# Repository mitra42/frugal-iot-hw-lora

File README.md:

# Frugal-IoT V0.3 LoRa

A simple, un-opinionated, multi-purpose sensor board, that can be wired to sensors using most common interfaces (I2C, ModBus, OneWire, Analog) with onboard charging and external antennas, plus a LoRa radio so boards can talk to each other where there is no WiFi.

This is the [Frugal-IoT V0.2 sensor board](https://github.com/mitra42/frugal-iot-hw-sensor) with an SX1262 LoRa radio added.

**Status:** laid out and routed, for review (31 Oct 2026): 84 × 37 mm, DRC clean, JLCPCB files ready but not ordered. About USD17.31 per board for 10 and USD11.58 for 100. See `DECISIONS.md` for requirements, decisions and the one open question (power budget with LoRa).

## Hardware Features

* ESP32-S3-WROOM-1U
* Ai-Thinker Ra-01SH LoRa radio (SX1262, 803–930 MHz), so one board covers AU915, AS923, IN865 and EU868 — the band is set in firmware.
* Two U.FL sockets for external antennas, one for WiFi (on the ESP32 module) and one for LoRa (on the radio module) — see [Antennas](#antennas).
* LoRa radio on its own always-on regulator, isolated from WiFi load and sleeping at under 1µA.
* USB-C for power and programming (e.g. using a $10 security camera solar panel)
* Protected charger circuitry for a single LiPo cell (~250mA), will work with really small cells (e.g. salvaged from vapes) or by adding a solder bridge can charge an 18650 cell at ~500mA
* Low-quiescent regulators (2µA each), so the board draws very little while asleep.
* Sensors controlled by a switched 3.3V sensor rail, allowing much lower power consumption in sleep.
* I2C support on J2
* Two sensor inputs on J2 (pins 6 & 9, GPIO4 & GPIO5) can be used for analog, OneWire etc, pads to add pull up resistor or smoothing capacitor if required.
* Two extra sensors on J3 (pins 6 & 9, GPIO1 & GPIO2)
* RS485(Modbus) on J3 pins 2 & 3, (can be omitted to save ~USD1.00, or the pins used as serial RX/TX instead).
* Six spare GPIOs on a 2 x 5 block of holes at the top edge, with GND and two switched 3.3V, for a header if ever needed.
* Test pads on every supply rail (VBUS, VBAT, VSYS, 3V3, 3V3_SW, 3V3_RF) and GND, labelled on the board.
* 37mm * 84mm board with connectors mostly at the ends, so that it can fit inside a 40mm pipe as an affordable enclosure.

## Antennas

Neither antenna is on the board or in `BOM.csv` (which is generated from the schematic) — buy them separately.

**Never transmit without the LoRa antenna connected**: the SX1262's output stage can be damaged driving an open socket.

The LoRa antenna plugs into the U.FL (IPEX MHF1) socket on the Ra-01SH. It must be a **50 Ω antenna for the
sub-GHz band** the board is configured for — 868 MHz (EU, Kenya, and 865–867 MHz India) or 915 MHz (Australia,
AS923 Indonesia). A 2.4 GHz WiFi antenna fits the same socket but works badly; the ESP32's own U.FL socket is
2.4 GHz, so label the two cables. Antennas marked "868/915" or "860–930 MHz" cover every region at some cost in
gain. When buying SMA parts, check SMA versus RP-SMA: they look alike and don't mate.

### Regular node

| Option | Parts | When |
|---|---|---|
| Whip through the end cap (recommended) | U.FL (MHF1) to SMA-female bulkhead pigtail, ~10–15 cm, 1.13 mm coax; 2–3 dBi SMA-male whip for the band | Nodes that relay for others or are far from their neighbours — range is the point of LoRa |
| Flexible PCB antenna inside the pipe | Adhesive FPC antenna with a U.FL lead | Short hops; no hole in the enclosure; cheapest. Expect less range: small FPC antennas are inefficient, so use the largest that fits |

Keep the antenna in a plastic (not metal) pipe, as far from the WiFi antenna, the cell and any wet soil as
the enclosure allows, and vertical if possible (nodes and gateway should share the same polarisation).

### Gateway node

The gateway is the same board (DECISIONS L11), but its antenna matters more because every node's traffic
passes through it.

* An outdoor omni antenna — fibreglass, 3–6 dBi, N-type, for the band (or 860–930 MHz), mast-mounted.
* Height beats gain: a few metres up, clear of roofs and trees, gains more than a higher-gain antenna low down.
* Keep the coax short. Thin cable loses several dB per metre at 900 MHz, so put the board (in its pipe) on the
  mast next to the antenna with a short pigtail, and run power or USB to it rather than RF. If a long RF run
  is unavoidable use low-loss coax (LMR-400 class).
* Seal the outdoor connectors (self-amalgamating tape) and earth the mast.
* Gain counts against the legal limit. With the SX1262 at its full +22 dBm, a 5.8 dBi antenna gives about
  28 dBm EIRP: inside Australia's 915–928 MHz limit (1 W EIRP) but far over Europe's 868 MHz limit
  (about 25 mW ERP in most sub-bands). Check the local rules (Kenya, India, Indonesia each set their own)
  and turn TX power down in firmware to match.

### Where to buy (low cost)

AliExpress listings, prices in USD as seen from Australia on 1 Nov 2026 without new-shopper deals; shipping
varies. Listings change and sellers' gain claims are optimistic, so check before ordering.

| For | Listing | Price | Per board |
|---|---|---|---|
| Node whip, 915 MHz | [NOWEPOCH, 3 dBi whip + U.FL-to-SMA bulkhead pigtail, pack of 4](https://www.aliexpress.com/item/1005008182646662.html) | 7.18 / 4 (6.35 at ≥10 packs) | 1.59–1.80 |
| Node whip, 868/915 MHz | [XYANT, 3 dBi whip + U.FL-to-SMA 15 cm pigtail, pack of 4](https://www.aliexpress.com/item/1005008633276903.html) | 7.79 / 4 (6.86 at ≥10 packs) | 1.72–1.95 |
| Node internal, 915 MHz | [CDEBYTE (Ebyte) TX915-FPC, 2.5 dBi, 10 per lot; sizes 3009, 4510, 7020, 8521 (length × width, mm)](https://www.aliexpress.com/item/1005010384153076.html) | 3.69–5.79 / 10 | 0.37–0.58 |
| Gateway antenna, 868 or 915 MHz | [GIZONT fibreglass omni, 35 cm, N-type, "5.8 dBi" (choose band variant)](https://www.aliexpress.com/item/1005012560449111.html) | 6.40–6.54 | — |
| Gateway pigtail | [U.FL (IPX1) to waterproof N-female bulkhead, RG178, 5 cm to 2 m](https://www.aliexpress.com/item/1005004546386028.html) | 3.60 (8 cm) | — |

Notes:
* For comparison, [Rokland's MHF1-to-SMA pigtails](https://store.rokland.com/products/2-pack-ufl-ipex4-mhf4-to-sma-female-pigtail-antenna-wifi-iot-dev-cable) alone are about USD 4 per board.
* The 868/915 whip is a compromise across both bands; the 915-only one should do a little better in AU/AS923.
* No 868 MHz version of the Ebyte FPC was found on AliExpress; for 868 regions use the whip, or find an 868 FPC.
  Choose the 8521 (85 × 21 mm) size if it fits — bigger is more efficient at sub-GHz.
* A real 5.8 dBi collinear at 868 MHz is usually much longer than 35 cm; treat the GIZONT as roughly 3 dBi.
  It is still a cheap, weatherproof outdoor antenna. Better-documented ones ([RAK](https://www.aliexpress.com/item/32852314761.html), [SparkFun](https://www.sparkfun.com/lora-fiberglass-antenna-type-n-5-8dbi-863-870mhz.html)) cost USD 40–120.
* RG178 loses roughly 1 dB per metre or more at 900 MHz: keep the gateway pigtail as short as the mounting allows.

## Software features

The board can be flashed with any software, but its designed to work well with [Frugal-IoT](https://github.com/mitra42/frugal-iot) which has the following features.

* Support for a very wide and expanding range of sensors
* Integrates with Frugal-IoT cloud, and UX on phone or laptop
* Plug and play MQTT interface, treats remote sensors and actuators the same as local ones
* LoRa mesh (using [LoRaMesher](https://github.com/LoRaMesher/LoRaMesher)), so sensors out of WiFi range report through other boards; any board can be the gateway to WiFi.
* Captive WiFi portal for local configuration
* Local controls for on-device automation configured through the UX.
* Multilingual support on both captive portal and UX
* Automatic Over-The-Air (OTA) updates for unattended devices (when on WiFi)
* Power management for really long life for sensors that report at long intervals.
* mDNS, for device to device signalling when the Internet is down
* NTP integration for accurate clock
* Fully Open-Source (i.e. not crippleware)

The radio is wired to the same ESP32-S3 pins as the Heltec WiFi LoRa 32 V3/V4, so firmware set up for those boards carries over.

## Files

| | |
|---|---|
| `SCHEMATIC.pdf` | schematic, one sheet |
| `BOM.csv` | bill of materials with LCSC (JLCPCB) part numbers; DNP = not fitted |
| `COST-ESTIMATE.txt` | JLCPCB cost for 10 and 100 boards, and the saving without Modbus |
| `PCB-LAYOUT.pdf` | 3D views and both copper layers |
| `fabrication/` | files to order from JLCPCB — see its README |
| `DECISIONS.md` | requirements, design decisions and why |
| `datasheets/` | Ai-Thinker Ra-01SH specification (Chinese; pinout, footprint and internal schematic) |
| `frugal_iot_v03/` | KiCad 10 project |
| `v0.2-baseline/` | the V0.2 board this started from: its README, decisions, schematic, layout, BOM, fabrication and firmware files |
| `claude-tools/` | scripts Claude uses to regenerate the design — reviewers can ignore |

The schematic is generated from `claude-tools/schematic/circuit.py`: changes made by Claude go there, not into
the .kicad_sch. Regenerate: `buildlib.py`, `run_draw_bg.sh` (log must end `VERIFY OK`), `run_kicad.sh`,
then `jlc_dump.sh` and `python3 cost_estimate.py > ../../COST-ESTIMATE.txt`.

If the fabrication and KiCad directories are not available wherever you find this, please let me know (mitra@mitra.biz) and I'll send you them.

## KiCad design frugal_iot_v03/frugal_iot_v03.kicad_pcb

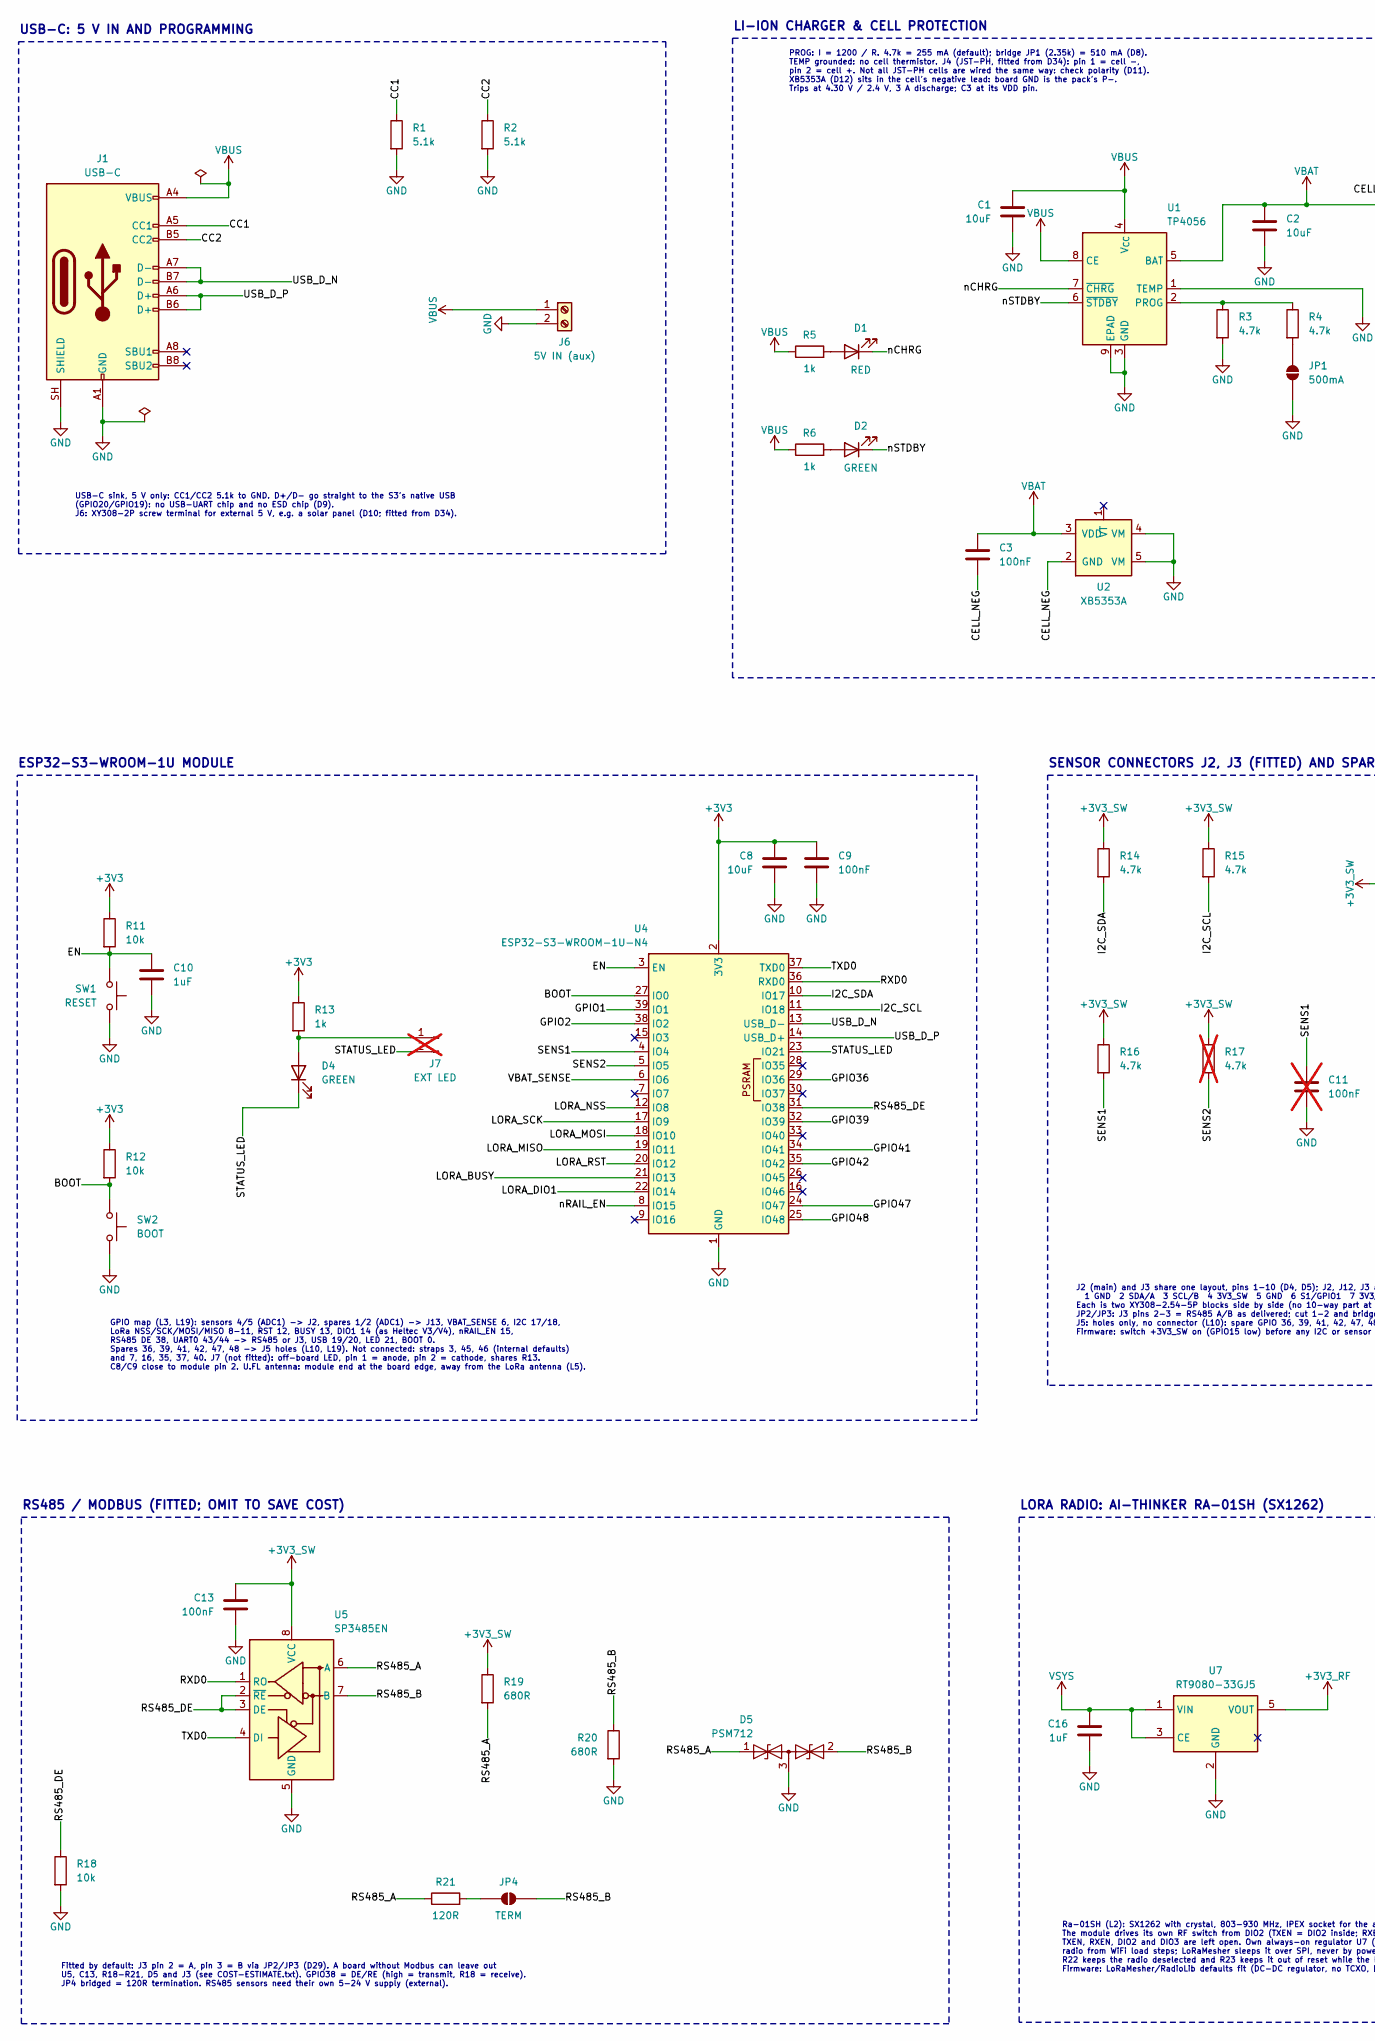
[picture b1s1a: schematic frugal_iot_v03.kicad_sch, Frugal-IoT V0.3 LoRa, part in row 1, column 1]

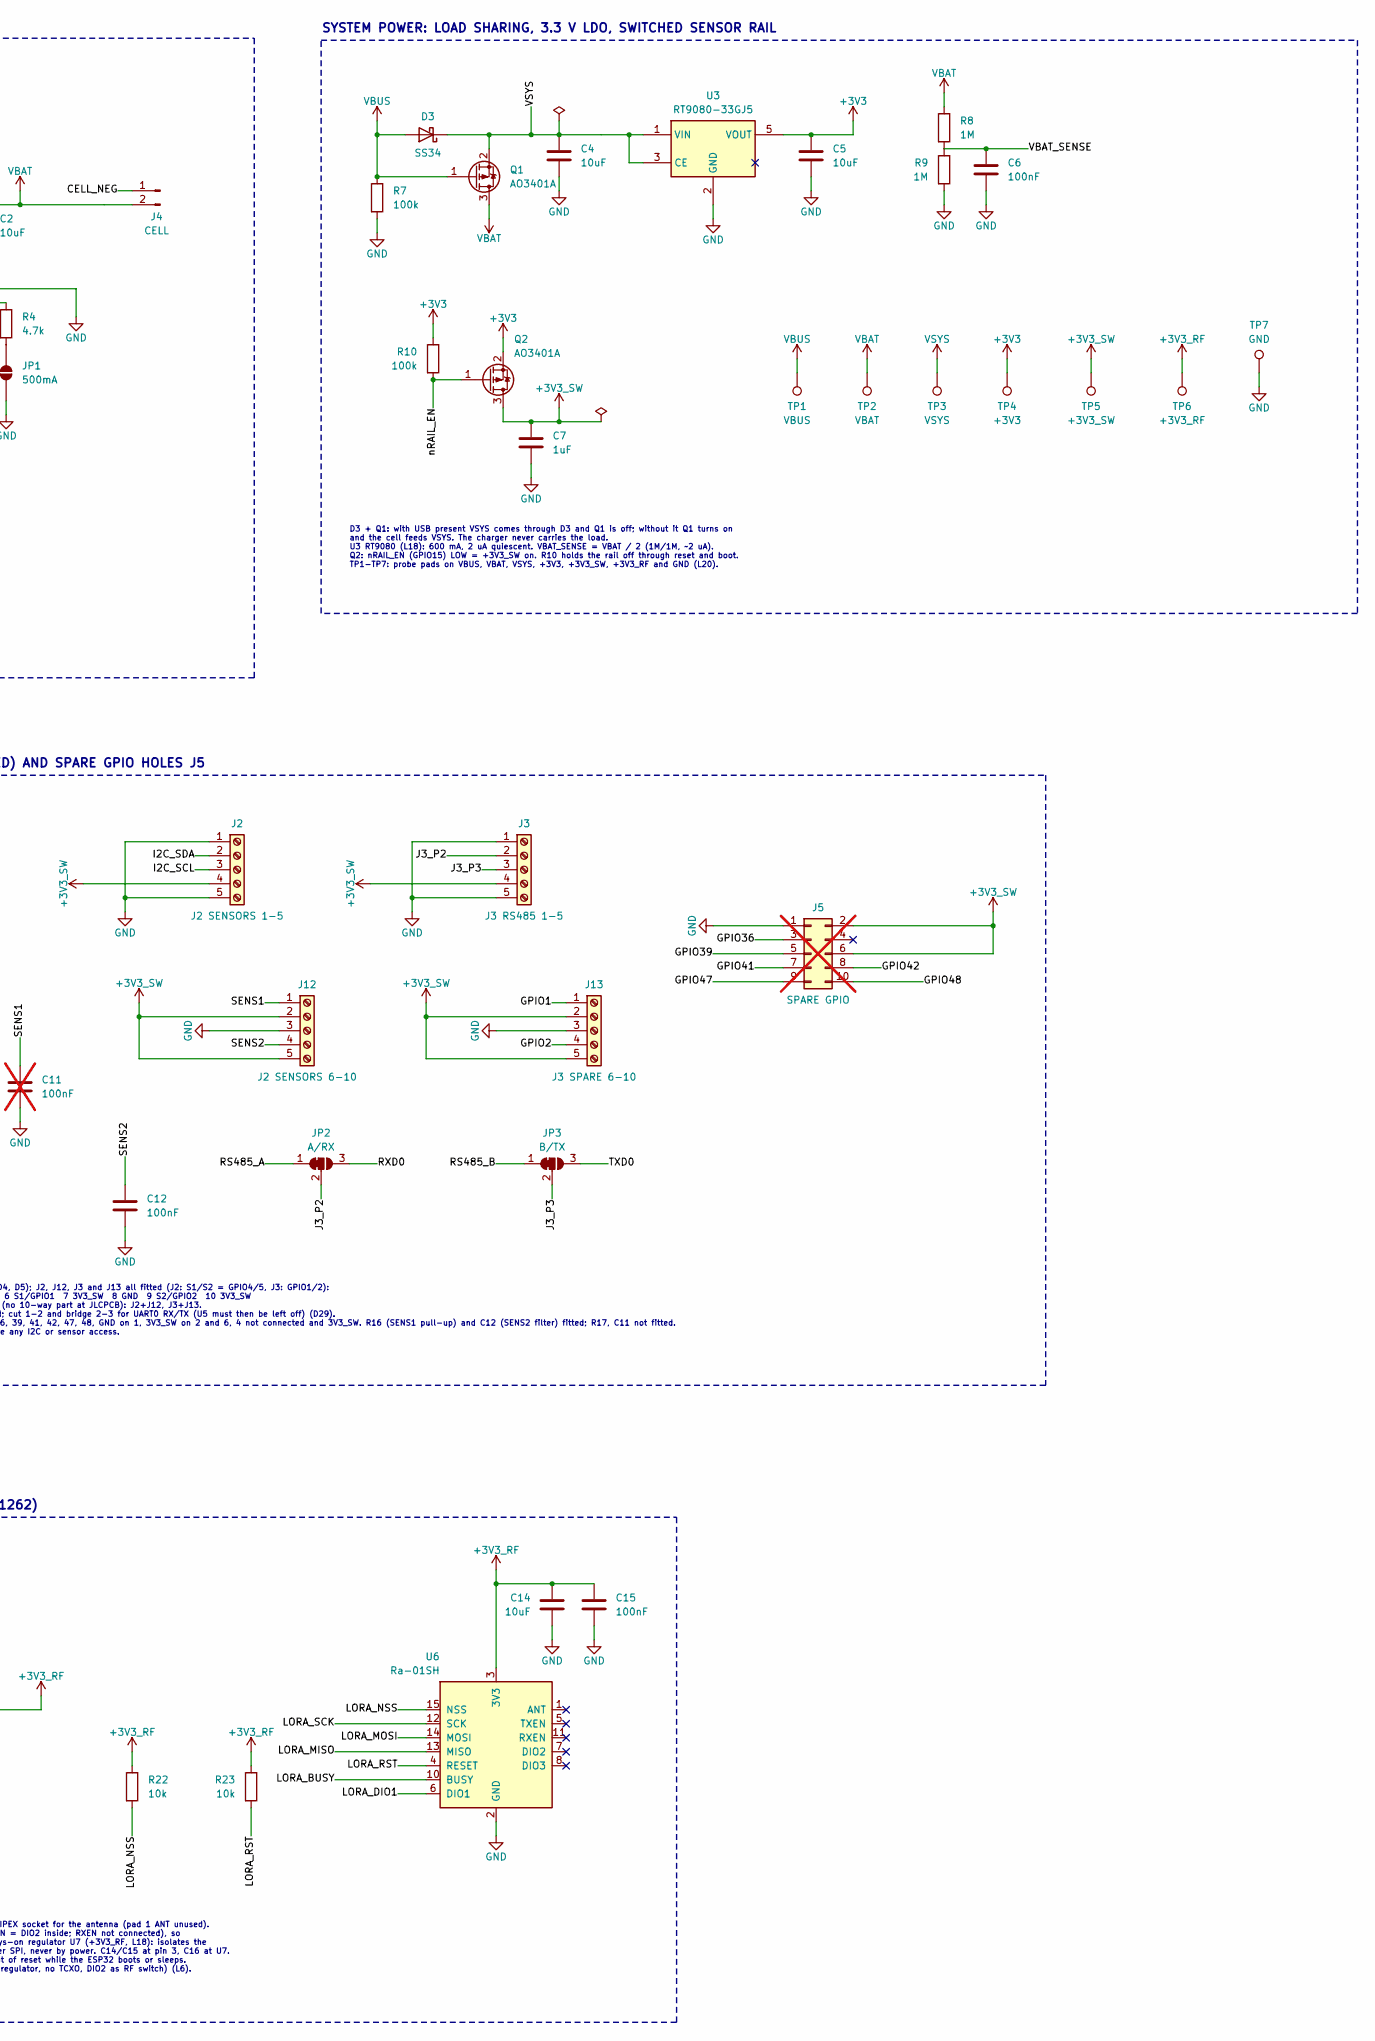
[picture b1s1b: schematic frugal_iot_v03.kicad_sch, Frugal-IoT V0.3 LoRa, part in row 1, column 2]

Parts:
C1, C2, C4, C5, C8, C14: 10uF; C_0603_1608Metric; MPN 10uF; LCSC C19702
C3, C6, C9, C12, C13, C15: 100nF; C_0603_1608Metric; MPN 100nF; LCSC C14663
C7, C10, C16: 1uF; C_0603_1608Metric; MPN 1uF; LCSC C15849
C11: 100nF; C_0603_1608Metric; MPN 100nF; LCSC C14663; not fitted
D1: RED; LED_0603_1608Metric; MPN KT-0603R; LCSC C2286
D2, D4: GREEN; LED_0805_2012Metric; MPN KT-0805G; LCSC C2297
D3: SS34; D_SMA; MPN SS34; LCSC C8678
D5: PSM712; SOT-23; MPN PSM712-LF-T7; LCSC C32677
J1: USB-C; USB_C_Receptacle_HRO_TYPE-C-31-M-12; MPN TYPE-C-31-M-12; LCSC C165948
J2: J2 SENSORS 1-5; TerminalBlock_Xinya_XY308-2.54-5P_1x05_P2.54mm_Horizontal; MPN XY308-2.54-5P; LCSC C915914
J3: J3 RS485 1-5; TerminalBlock_Xinya_XY308-2.54-5P_1x05_P2.54mm_Horizontal; MPN XY308-2.54-5P; LCSC C915914
J4: CELL; JST_PH_S2B-PH-K_1x02_P2.00mm_Horizontal; MPN S2B-PH-K-S; LCSC C173752
J5: SPARE GPIO; PinHeader_2x05_P2.54mm_Vertical; MPN SPARE GPIO; not fitted
J6: 5V IN (aux); TerminalBlock_Xinya_XY308-2.54-2P_1x02_P2.54mm_Horizontal; MPN XY308-2.54-2P; LCSC C557685
J7: EXT LED; PinHeader_1x02_P2.54mm_Vertical; MPN EXT LED; not fitted
J12: J2 SENSORS 6-10; TerminalBlock_Xinya_XY308-2.54-5P_1x05_P2.54mm_Horizontal; MPN XY308-2.54-5P; LCSC C915914
J13: J3 SPARE 6-10; TerminalBlock_Xinya_XY308-2.54-5P_1x05_P2.54mm_Horizontal; MPN XY308-2.54-5P; LCSC C915914
JP1: 500mA; SolderJumper-2_P1.3mm_Open_RoundedPad1.0x1.5mm; MPN 500mA
JP2: A/RX; SolderJumper-3_P1.3mm_Bridged12_RoundedPad1.0x1.5mm; MPN A/RX
JP3: B/TX; SolderJumper-3_P1.3mm_Bridged12_RoundedPad1.0x1.5mm; MPN B/TX
JP4: TERM; SolderJumper-2_P1.3mm_Open_RoundedPad1.0x1.5mm; MPN TERM
Q1, Q2: AO3401A; SOT-23; MPN AO3401A; LCSC C15127
R1, R2: 5.1k; R_0603_1608Metric; MPN 5.1k; LCSC C23186
R3, R4, R14, R15, R16: 4.7k; R_0603_1608Metric; MPN 4.7k; LCSC C23162
R5, R6, R13: 1k; R_0603_1608Metric; MPN 1k; LCSC C21190
R7, R10: 100k; R_0603_1608Metric; MPN 100k; LCSC C25803
R8, R9: 1M; R_0603_1608Metric; MPN 1M; LCSC C22935
R11, R12, R18, R22, R23: 10k; R_0603_1608Metric; MPN 10k; LCSC C25804
R17: 4.7k; R_0603_1608Metric; MPN 4.7k; LCSC C23162; not fitted
R19, R20: 680R; R_0603_1608Metric; MPN 680R; LCSC C23228
R21: 120R; R_0603_1608Metric; MPN 120R; LCSC C22787
SW1: RESET; SW_Push_1P1T_XKB_TS-1187A; MPN TS-1187A-B-A-B; LCSC C318884
SW2: BOOT; SW_Push_1P1T_XKB_TS-1187A; MPN TS-1187A-B-A-B; LCSC C318884
TP1: VBUS; TestPoint_Pad_D1.5mm; MPN VBUS
TP2: VBAT; TestPoint_Pad_D1.5mm; MPN VBAT
TP3: VSYS; TestPoint_Pad_D1.5mm; MPN VSYS
TP4: +3V3; TestPoint_Pad_D1.5mm; MPN +3V3
TP5: +3V3_SW; TestPoint_Pad_D1.5mm; MPN +3V3_SW
TP6: +3V3_RF; TestPoint_Pad_D1.5mm; MPN +3V3_RF
TP7: GND; TestPoint_Pad_D1.5mm; MPN GND
U1: TP4056; SOIC-8-1EP_3.9x4.9mm_P1.27mm_EP2.41x3.3mm; MPN TP4056; LCSC C16581
U2: XB5353A; SOT-23-5; MPN XB5353A; LCSC C80628
U3, U7: RT9080-33GJ5; TSOT-23-5; MPN RT9080-33GJ5; LCSC C841192
U4: ESP32-S3-WROOM-1U-N4; ESP32-S3-WROOM-1U; MPN ESP32-S3-WROOM-1U-N4; LCSC C2980296
U5: SP3485EN; SOIC-8_3.9x4.9mm_P1.27mm; MPN SP3485EN-L/TR; LCSC C8963
U6: Ra-01SH; Ai-Thinker-Ra-01SH; MPN Ra-01SH; LCSC C2764087

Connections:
+3V3: C5.1, C8.1, C9.1, Q2.2 (S), R10.1, R11.1, R12.1, R13.1, TP4.1, U3.5 (VOUT), U4.2 (3V3)
+3V3_RF: C14.1, C15.1, R22.1, R23.1, TP6.1, U6.3 (3V3), U7.5 (VOUT)
/BOOT: R12.2, SW2.1, U4.27 (IO0)
/CC1: J1.A5 (CC1), R1.1
/CC2: J1.B5 (CC2), R2.1
/CELL_NEG: C3.2, J4.1, U2.2 (GND)
/EN: C10.1, R11.2, SW1.1, U4.3 (EN)
/GPIO1: J13.1, U4.39 (IO1)
/GPIO2: J13.4, U4.38 (IO2)
/GPIO36: J5.3, U4.29 (IO36)
/GPIO39: J5.5, U4.32 (IO39)
/GPIO41: J5.7, U4.34 (IO41)
/GPIO42: J5.8, U4.35 (IO42)
/GPIO47: J5.9, U4.24 (IO47)
/GPIO48: J5.10, U4.25 (IO48)
/I2C_SCL: J2.3, R15.2, U4.11 (IO18)
/I2C_SDA: J2.2, R14.2, U4.10 (IO17)
/J3_P2: J3.2, JP2.2 (C)
/J3_P3: J3.3, JP3.2 (C)
/LORA_BUSY: U4.21 (IO13), U6.10 (BUSY)
/LORA_DIO1: U4.22 (IO14), U6.6 (DIO1)
/LORA_MISO: U4.19 (IO11), U6.13 (MISO)
/LORA_MOSI: U4.18 (IO10), U6.14 (MOSI)
/LORA_NSS: R22.2, U4.12 (IO8), U6.15 (NSS)
/LORA_RST: R23.2, U4.20 (IO12), U6.4 (RESET)
/LORA_SCK: U4.17 (IO9), U6.12 (SCK)
/RS485_A: D5.1 (A1), JP2.1 (A), R19.2, R21.1, U5.6 (A)
/RS485_B: D5.2 (A2), JP3.1 (A), JP4.2 (B), R20.1, U5.7 (B)
/RS485_DE: R18.1, U4.31 (IO38), U5.2 (~RE), U5.3 (DE)
/RXD0: JP2.3 (B), U4.36 (RXD0), U5.1 (RO)
/SENS1: C11.1, J12.1, R16.2, U4.4 (IO4)
/SENS2: C12.1, J12.4, R17.2, U4.5 (IO5)
/STATUS_LED: D4.1 (K), J7.2, U4.23 (IO21)
/TXD0: JP3.3 (B), U4.37 (TXD0), U5.4 (DI)
/USB_D_N: J1.A7 (D-), J1.B7 (D-), U4.13 (USB_D-)
/USB_D_P: J1.A6 (D+), J1.B6 (D+), U4.14 (USB_D+)
/VBAT_SENSE: C6.1, R8.2, R9.1, U4.6 (IO6)
/nCHRG: D1.1 (K), U1.7 (~CHRG)
/nRAIL_EN: Q2.1 (G), R10.2, U4.8 (IO15)
/nSTDBY: D2.1 (K), U1.6 (~STDBY)
unnamed: D1.2 (A), R5.2
unnamed: D2.2 (A), R6.2
unnamed: D4.2 (A), J7.1, R13.2
unnamed: JP1.1 (A), R4.2
unnamed: JP4.1 (A), R21.2
unnamed: R3.1, R4.1, U1.2 (PROG)
VBAT: C2.1, C3.1, J4.2, Q1.3 (D), R8.1, TP2.1, U1.5 (BAT), U2.3 (VDD)

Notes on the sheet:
J2 (main) and J3 share one layout, pins 1-10 (D4, D5); J2, J12, J3 and J13 all fitted (J2: S1/S2 = GPIO4/5, J3: GPIO1/2): 1 GND 2 SDA/A 3 SCL/B 4 3V3_SW 5 GND 6 S1/GPIO1 7 3V3_SW 8 GND 9 S2/GPIO2 10 3V3_SW Each is two XY308-2.54-5P blocks side by side (no 10-way part at JLCPCB): J2+J12, J3+J13. JP2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
USB-C sink, 5 V only: CC1/CC2 5.1k to GND. D+/D- go straight to the S3's native USB (GPIO20/GPIO19): no USB-UART chip and no ESD chip (D9). J6: XY308-2P screw terminal for external 5 V, e.g. a solar panel (D10; fitted from D34).
PROG: I = 1200 / R. 4.7k = 255 mA (default); bridge JP1 (2.35k) = 510 mA (D8). TEMP grounded: no cell thermistor. J4 (JST-PH, fitted from D34): pin 1 = cell -, pin 2 = cell +. Not all JST-PH cells are wired the same way: check polarity (D11). XB5353A (D12) sits in the cell's negative lead: board GN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
ESP32-S3-WROOM-1U MODULE
Ra-01SH (L2): SX1262 with crystal, 803-930 MHz, IPEX socket for the antenna (pad 1 ANT unused). The module drives its own RF switch from DIO2 (TXEN = DIO2 inside; RXEN not connected), so TXEN, RXEN, DIO2 and DIO3 are left open. Own always-on regulator U7 (+3V3_RF, L18): isolates the radio from WiFi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
Fitted by default: J3 pin 2 = A, pin 3 = B via JP2/JP3 (D29). A board without Modbus can leave out U5, C13, R18-R21, D5 and J3 (see COST-ESTIMATE.txt). GPIO38 = DE/RE (high = transmit, R18 = receive). JP4 bridged = 120R termination. RS485 sensors need their own 5-24 V supply (external).
USB-C: 5 V IN AND PROGRAMMING
SYSTEM POWER: LOAD SHARING, 3.3 V LDO, SWITCHED SENSOR RAIL
LORA RADIO: AI-THINKER RA-01SH (SX1262)
GPIO map (L3, L19): sensors 4/5 (ADC1) -> J2, spares 1/2 (ADC1) -> J13, VBAT_SENSE 6, I2C 17/18, LoRa NSS/SCK/MOSI/MISO 8-11, RST 12, BUSY 13, DIO1 14 (as Heltec V3/V4), nRAIL_EN 15, RS485 DE 38, UART0 43/44 -> RS485 or J3, USB 19/20, LED 21, BOOT 0. Spares 36, 39, 41, 42, 47, 48 -> J5 holes (L10, 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
RS485 / MODBUS (FITTED; OMIT TO SAVE COST)
SENSOR CONNECTORS J2, J3 (FITTED) AND SPARE GPIO HOLES J5
D3 + Q1: with USB present VSYS comes through D3 and Q1 is off; without it Q1 turns on and the cell feeds VSYS. The charger never carries the load. U3 RT9080 (L18): 600 mA, 2 uA quiescent. VBAT_SENSE = VBAT / 2 (1M/1M, ~2 uA). Q2: nRAIL_EN (GPIO15) LOW = +3V3_SW on. R10 holds the rail off through re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
LI-ION CHARGER & CELL PROTECTION

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
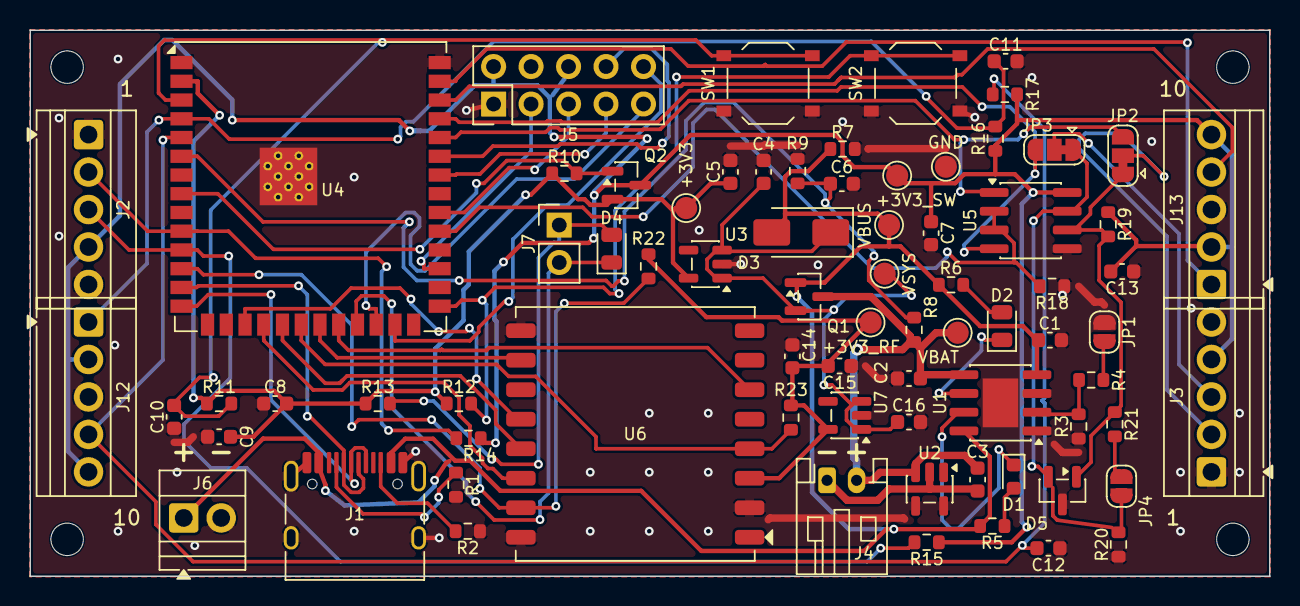
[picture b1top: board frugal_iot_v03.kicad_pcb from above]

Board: 2 copper layers, 84.0 x 37.0 mm, 79 parts (0 on the bottom side), 51 nets.

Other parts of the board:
H1, H2, H3, H4: M2; MountingHole_2.2mm_M2

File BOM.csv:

"Refs","Value","MPN","LCSC","Footprint","Qty","DNP","Note"
"C1,C2,C4,C5,C8,C14","10uF","10uF","C19702","Capacitor_SMD:C_0603_1608Metric","6","",""
"C3,C6,C9,C12,C13,C15","100nF","100nF","C14663","Capacitor_SMD:C_0603_1608Metric","6","","filter (analog)"
"C7,C10,C16","1uF","1uF","C15849","Capacitor_SMD:C_0603_1608Metric","3","","U7 input, close to its VIN"
"C11","100nF","100nF","C14663","Capacitor_SMD:C_0603_1608Metric","1","DNP","filter option (analog)"
"D1","RED","KT-0603R","C2286","LED_SMD:LED_0603_1608Metric","1","",""
"D2,D4","GREEN","KT-0805G","C2297","LED_SMD:LED_0805_2012Metric","2","",""
"D3","SS34","SS34","C8678","Diode_SMD:D_SMA","1","",""
"D5","PSM712","PSM712-LF-T7","C32677","Package_TO_SOT_SMD:SOT-23","1","",""
"J1","USB-C","TYPE-C-31-M-12","C165948","Connector_USB:USB_C_Receptacle_HRO_TYPE-C-31-M-12","1","",""
"J2","J2 SENSORS 1-5","XY308-2.54-5P","C915914","TerminalBlock:TerminalBlock_Xinya_XY308-2.54-5P_1x05_P2.54mm_Horizontal","1","",""
"J3","J3 RS485 1-5","XY308-2.54-5P","C915914","TerminalBlock:TerminalBlock_Xinya_XY308-2.54-5P_1x05_P2.54mm_Horizontal","1","",""
"J4","CELL","S2B-PH-K-S","C173752","Connector_JST:JST_PH_S2B-PH-K_1x02_P2.00mm_Horizontal","1","",""
"J5","SPARE GPIO","SPARE GPIO","","Connector_PinHeader_2.54mm:PinHeader_2x05_P2.54mm_Vertical","1","DNP","holes only (L10)"
"J6","5V IN (aux)","XY308-2.54-2P","C557685","TerminalBlock:TerminalBlock_Xinya_XY308-2.54-2P_1x02_P2.54mm_Horizontal","1","",""
"J7","EXT LED","EXT LED","","Connector_PinHeader_2.54mm:PinHeader_1x02_P2.54mm_Vertical","1","DNP","off-board LED: 1 = anode, 2 = cathode"
"J12","J2 SENSORS 6-10","XY308-2.54-5P","C915914","TerminalBlock:TerminalBlock_Xinya_XY308-2.54-5P_1x05_P2.54mm_Horizontal","1","",""
"J13","J3 SPARE 6-10","XY308-2.54-5P","C915914","TerminalBlock:TerminalBlock_Xinya_XY308-2.54-5P_1x05_P2.54mm_Horizontal","1","",""
"JP1","500mA","500mA","","Jumper:SolderJumper-2_P1.3mm_Open_RoundedPad1.0x1.5mm","1","",""
"JP2","A/RX","A/RX","","Jumper:SolderJumper-3_P1.3mm_Bridged12_RoundedPad1.0x1.5mm","1","",""
"JP3","B/TX","B/TX","","Jumper:SolderJumper-3_P1.3mm_Bridged12_RoundedPad1.0x1.5mm","1","",""
"JP4","TERM","TERM","","Jumper:SolderJumper-2_P1.3mm_Open_RoundedPad1.0x1.5mm","1","",""
"Q1,Q2","AO3401A","AO3401A","C15127","Package_TO_SOT_SMD:SOT-23","2","",""
"R1,R2","5.1k","5.1k","C23186","Resistor_SMD:R_0603_1608Metric","2","",""
"R3,R4,R14-R16","4.7k","4.7k","C23162","Resistor_SMD:R_0603_1608Metric","5","","pull-up (e.g. DS18B20),with JP1: ~500 mA,~250 mA"
"R5,R6,R13","1k","1k","C21190","Resistor_SMD:R_0603_1608Metric","3","",""
"R7,R10","100k","100k","C25803","Resistor_SMD:R_0603_1608Metric","2","","rail off at reset"
"R8,R9","1M","1M","C22935","Resistor_SMD:R_0603_1608Metric","2","",""
"R11,R12,R18,R22,R23","10k","10k","C25804","Resistor_SMD:R_0603_1608Metric","5","","radio deselected while the ESP32 boots or sleeps,radio out of reset while the ESP32 sleeps,receive by default"
"R17","4.7k","4.7k","C23162","Resistor_SMD:R_0603_1608Metric","1","DNP","pull-up option (e.g. DS18B20)"
"R19,R20","680R","680R","C23228","Resistor_SMD:R_0603_1608Metric","2","","bias"
"R21","120R","120R","C22787","Resistor_SMD:R_0603_1608Metric","1","",""
"SW1","RESET","TS-1187A-B-A-B","C318884","Button_Switch_SMD:SW_Push_1P1T_XKB_TS-1187A","1","",""
"SW2","BOOT","TS-1187A-B-A-B","C318884","Button_Switch_SMD:SW_Push_1P1T_XKB_TS-1187A","1","",""
"TP1","VBUS","VBUS","","TestPoint:TestPoint_Pad_D1.5mm","1","",""
"TP2","VBAT","VBAT","","TestPoint:TestPoint_Pad_D1.5mm","1","",""
"TP3","VSYS","VSYS","","TestPoint:TestPoint_Pad_D1.5mm","1","",""
"TP4","+3V3","+3V3","","TestPoint:TestPoint_Pad_D1.5mm","1","",""
"TP5","+3V3_SW","+3V3_SW","","TestPoint:TestPoint_Pad_D1.5mm","1","",""
"TP6","+3V3_RF","+3V3_RF","","TestPoint:TestPoint_Pad_D1.5mm","1","",""
"TP7","GND","GND","","TestPoint:TestPoint_Pad_D1.5mm","1","",""
"U1","TP4056","TP4056","C16581","Package_SO:SOIC-8-1EP_3.9x4.9mm_P1.27mm_EP2.41x3.3mm","1","","TEMP grounded: no cell NTC"
"U2","XB5353A","XB5353A","C80628","Package_TO_SOT_SMD:SOT-23-5","1","",""
"U3,U7","RT9080-33GJ5","RT9080-33GJ5","C841192","Package_TO_SOT_SMD:TSOT-23-5","2","",""
"U4","ESP32-S3-WROOM-1U-N4","ESP32-S3-WROOM-1U-N4","C2980296","RF_Module:ESP32-S3-WROOM-1U","1","",""
"U5","SP3485EN","SP3485EN-L/TR","C8963","Package_SO:SOIC-8_3.9x4.9mm_P1.27mm","1","",""
"U6","Ra-01SH","Ra-01SH","C2764087","frugal:Ai-Thinker-Ra-01SH","1","",""

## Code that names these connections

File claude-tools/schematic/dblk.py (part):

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        S.wire(pa, (xj, pa[1])); S.wire(pb, (xj, pb[1])); S.wire((xj, pa[1]), (xj, pb[1]))
        qa, qb = pin('J1', 'A6'), pin('J1', 'B6')
        S.wire(qa, (xj, qa[1])); S.wire(qb, (xj, qb[1])); S.wire((xj, qa[1]), (xj, qb[1]))
        S.wire((xj, pb[1]), (xj + 7.62, pb[1])); S.label('USB_D_N', xj + 7.62, pb[1])
        S.wire((xj, qa[1]), (xj + 7.62, qa[1])); S.label('USB_D_P', xj + 7.62, qa[1])
        # CC pull-downs
        cx = n1[0] + 30.48
        for ref, net in (('R1', 'CC1'), ('R2', 'CC2')):
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        c = at(n, -10.16)
        S.wire(n, c)
        cb = hang('C3', c)
        S.wire(cb, at(cb, 0, 2.54)); S.label('CELL_NEG', cb[0], cb[1] + 2.54, angle=270)
        g = pin('U2', '2')
        S.wire(g, at(g, -2.54), at(g, -2.54, 5.08)); S.label('CELL_NEG', g[0] - 2.54, g[1] + 5.08, angle=270)
        p4, p5 = pin('U2', '4'), pin('U2', '5')
        e4, e5 = at(p4, 5.08), at(p5, 5.08)
        S.wire(p4, e4); S.wire(p5, e5); S.wire(e4, e5)
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        m = hang('R8', (bx, by))
        hang('R9', m, 'GND')
        c = at(m, 7.62); S.wire(m, c); hang('C6', c, 'GND')
        S.wire(c, at(c, 5.08)); S.label('VBAT_SENSE', c[0] + 5.08, c[1])
        # switched sensor rail: P-FET, gate pulled up to +3V3 (off), GPIO5 low = on
        sx, sy = x + 20.32, y + 38.1
        put('Q2', sx, sy, mirror='x')
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        gn = at(g, -5.08)
        S.wire(g, gn)
        rise('R10', gn, '+3V3', bottom_pin='2')
        S.wire(gn, at(gn, 0, 5.08)); S.label('nRAIL_EN', gn[0], gn[1] + 5.08, angle=270)
        # test points (L20): one per supply rail, plus GND for the probe's ground
        for i in range(7):
            ref = f'TP{i + 1}'
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        S.note("D3 + Q1: with USB present VSYS comes through D3 and Q1 is off; without it Q1 turns on\n"
               "and the cell feeds VSYS. The charger never carries the load.\n"
               "U3 RT9080 (L18): 600 mA, 2 uA quiescent. VBAT_SENSE = VBAT / 2 (1M/1M, ~2 uA).\n"
               "Q2: nRAIL_EN (GPIO15) LOW = +3V3_SW on. R10 holds the rail off through reset and boot.\n"
               "TP1-TP7: probe pads on VBUS, VBAT, VSYS, +3V3, +3V3_SW, +3V3_RF and GND (L20).",
               x - 5.08, y + 58.42, 1.0)

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        S.wire(r2, pin('D4', '2'))
        kk = pin('D4', '1')
        S.wire(kk, (kk[0], n[1]), n)
        S.wire(n, at(n, 0, 5.08)); S.label('STATUS_LED', n[0], n[1] + 5.08, angle=270)
        put_pin('J7', '1', at(r2, 20.32), mirror='y')
        S.wire(r2, pin('J7', '1'))
        term('J7', '2', 'STATUS_LED', 2.54)
        S.note("GPIO map (L3, L19): sensors 4/5 (ADC1) -> J2, spares 1/2 (ADC1) -> J13, VBAT_SENSE 6, I2C 17/18,\n"
               "LoRa NSS/SCK/MOSI/MISO 8-11, RST 12, BUSY 13, DIO1 14 (as Heltec V3/V4), nRAIL_EN 15,\n"
               "RS485 DE 38, UART0 43/44 -> RS485 or J3, USB 19/20, LED 21, BOOT 0.\n"
               "Spares 36, 39, 41, 42, 47, 48 -> J5 holes (L10, L19). Not connected: straps 3, 45, 46 (internal defaults)\n"
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        nets = {'J2': ['GND', 'I2C_SDA', 'I2C_SCL', '+3V3_SW', 'GND'],
                'J12': ['SENS1', '+3V3_SW', 'GND', 'SENS2', '+3V3_SW'],
                'J3': ['GND', 'J3_P2', 'J3_P3', '+3V3_SW', 'GND'],
                'J13': ['GPIO1', '+3V3_SW', 'GND', 'GPIO2', '+3V3_SW']}
        for i, ref in enumerate(('J2', 'J12')):
            put(ref, jx, y - 2.54 + 17.78 * i)
            for k, net in enumerate(nets[ref]):
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        put('J5', jx + 91.44, y + 12.7)
        signals('J5')
        term('J5', '1', 'GND', RL['GND']); term('J5', '2', '+3V3_SW', RL['+3V3_SW']); term('J5', '6', '+3V3_SW', RL['+3V3_SW'])
        S.note("J2 (main) and J3 share one layout, pins 1-10 (D4, D5); J2, J12, J3 and J13 all fitted (J2: S1/S2 = GPIO4/5, J3: GPIO1/2):\n"
               "  1 GND  2 SDA/A  3 SCL/B  4 3V3_SW  5 GND  6 S1/GPIO1  7 3V3_SW  8 GND  9 S2/GPIO2  10 3V3_SW\n"
               "Each is two XY308-2.54-5P blocks side by side (no 10-way part at JLCPCB): J2+J12, J3+J13.\n"
               "JP2/JP3: J3 pins 2-3 = RS485 A/B as delivered; cut 1-2 and bridge 2-3 for UART0 RX/TX (U5 must then be left off) (D29).\n"
               "J5: holes only, no connector (L10): spare GPIO 36, 39, 41, 42, 47, 48, GND on 1, 3V3_SW on 2 and 6, 4 not connected and 3V3_SW. R16 (SENS1 pull-up) and C12 (SENS2 filter) fitted; R17, C11 not fitted.\n"
               "Firmware: switch +3V3_SW on (GPIO15 low) before any I2C or sensor access.",
               x - 5.08, y + 76.2, 1.0)

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        p2, p3 = pin('U5', '2'), pin('U5', '3')
        j2, j3 = at(p2, -2.54), at(p3, -2.54)
        S.wire(p2, j2); S.wire(p3, j3); S.wire(j2, j3)
        S.wire(j3, at(j3, -5.08)); S.label('RS485_DE', j3[0] - 5.08, j3[1], angle=180)
        v = pin('U5', '8')
        m = at(v, 0, -7.62); t = at(v, 0, -10.16)
        S.wire(v, m, t); port('+3V3_SW', *t)
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        lab_up('R19', (bx, y), 'RS485_A', '+3V3_SW')
        lab_down('R20', (bx + 12.7, y + 2.54), 'RS485_B', 'GND')
        st = (bx - 5.08, y + 25.4)
        S.wire(at(st, -5.08), st); S.label('RS485_A', st[0] - 5.08, st[1], angle=180)
        e = series('R21', st)
        S.wire(e, at(e, 2.54))
        series('JP4', at(e, 2.54), first='1', rot=0)
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
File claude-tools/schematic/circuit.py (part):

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     {'1': 'VSYS', '3': 'VSYS', '2': 'GND', '4': 'NC', '5': '+3V3'}, B, lcsc='C841192', mpn='RT9080-33GJ5')
C('10uF', '+3V3', 'GND', B)
R('1M', 'VBAT', 'VBAT_SENSE', B); R('1M', 'VBAT_SENSE', 'GND', B); C('100nF', 'VBAT_SENSE', 'GND', B)
PFET('nRAIL_EN', '+3V3', '+3V3_SW', B)           # GPIO5 low = sensors on; pull-up keeps it off at reset
R('100k', '+3V3', 'nRAIL_EN', B, note='rail off at reset')
C('1uF', '+3V3_SW', 'GND', B)

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      '8': 'nRAIL_EN', '9': 'NC', '10': 'I2C_SDA', '11': 'I2C_SCL', '12': 'LORA_NSS',
      '13': 'USB_D_N', '14': 'USB_D_P', '15': 'NC', '16': 'NC', '17': 'LORA_SCK', '18': 'LORA_MOSI',
      '19': 'LORA_MISO', '20': 'LORA_RST', '21': 'LORA_BUSY', '22': 'LORA_DIO1', '23': 'STATUS_LED',
      '24': 'GPIO47', '25': 'GPIO48', '26': 'NC', '27': 'BOOT', '28': 'NC', '29': 'GPIO36', '30': 'NC',
      '31': 'RS485_DE', '32': 'GPIO39', '33': 'NC', '34': 'GPIO41', '35': 'GPIO42',
      '36': 'RXD0', '37': 'TXD0', '38': 'GPIO2', '39': 'GPIO1', '40': 'GND', '41': 'GND'},
     B, lcsc='C2980296', mpn='ESP32-S3-WROOM-1U-N4')
C('10uF', '+3V3', 'GND', B); C('100nF', '+3V3', 'GND', B)
R('10k', '+3V3', 'EN', B); C('1uF', 'EN', 'GND', B); BUTTON('EN', 'GND', B, 'RESET')
R('10k', '+3V3', 'BOOT', B); BUTTON('BOOT', 'GND', B, 'BOOT')
R('1k', '+3V3', 'LED_STAT', B); LED('GREEN', 'LED_STAT', 'STATUS_LED', B)
part('J', 'Connector:Conn_01x02_Pin', 'EXT LED', HDR.format(n=2), {'1': 'LED_STAT', '2': 'STATUS_LED'}, B,
     dnp=True, ref='J7', note='off-board LED: 1 = anode, 2 = cathode')

# ---------------- Sensor connectors ----------------
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TERM('J12', 5, ['SENS1', '+3V3_SW', 'GND', 'SENS2', '+3V3_SW'], B, 'J2 SENSORS 6-10')
# J3: same layout (D5); pins 2-3 = RS485 A/B as delivered (JP2/JP3 bridged 1-2), or UART RX/TX (cut, bridge 2-3)
TERM('J3', 5, ['GND', 'J3_P2', 'J3_P3', '+3V3_SW', 'GND'], B, 'J3 RS485 1-5')   # Modbus fitted (L9)
TERM('J13', 5, ['GPIO1', '+3V3_SW', 'GND', 'GPIO2', '+3V3_SW'], B, 'J3 SPARE 6-10')
part('JP', 'Jumper:SolderJumper_3_Bridged12', 'A/RX', SJ3, {'1': 'RS485_A', '2': 'J3_P2', '3': 'RXD0'}, B)
part('JP', 'Jumper:SolderJumper_3_Bridged12', 'B/TX', SJ3, {'1': 'RS485_B', '2': 'J3_P3', '3': 'TXD0'}, B)
# J5: spare GPIOs on a 2 x 5 block of unfitted 2.54 mm holes (L10; 2 x 5 rather than a row, for layout, L19).
# Hole 6 is a second 3V3_SW; hole 4 is unconnected (boxed in by tracks): GPIO37/40 could not be routed to
# either (L19, Mitra 31 Oct).
part('J', 'Connector_Generic:Conn_02x05_Odd_Even', 'SPARE GPIO', 'Connector_PinHeader_2.54mm:PinHeader_2x05_P2.54mm_Vertical',
     {'1': 'GND', '2': '+3V3_SW', '3': 'GPIO36', '4': 'NC', '5': 'GPIO39', '6': '+3V3_SW', '7': 'GPIO41',
      '8': 'GPIO42', '9': 'GPIO47', '10': 'GPIO48'}, B, dnp=True, ref='J5', note='holes only (L10)')

# ---------------- RS485 (fitted by default, L9 / D29; omit to save cost) ----------------
B = 'rs485'
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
